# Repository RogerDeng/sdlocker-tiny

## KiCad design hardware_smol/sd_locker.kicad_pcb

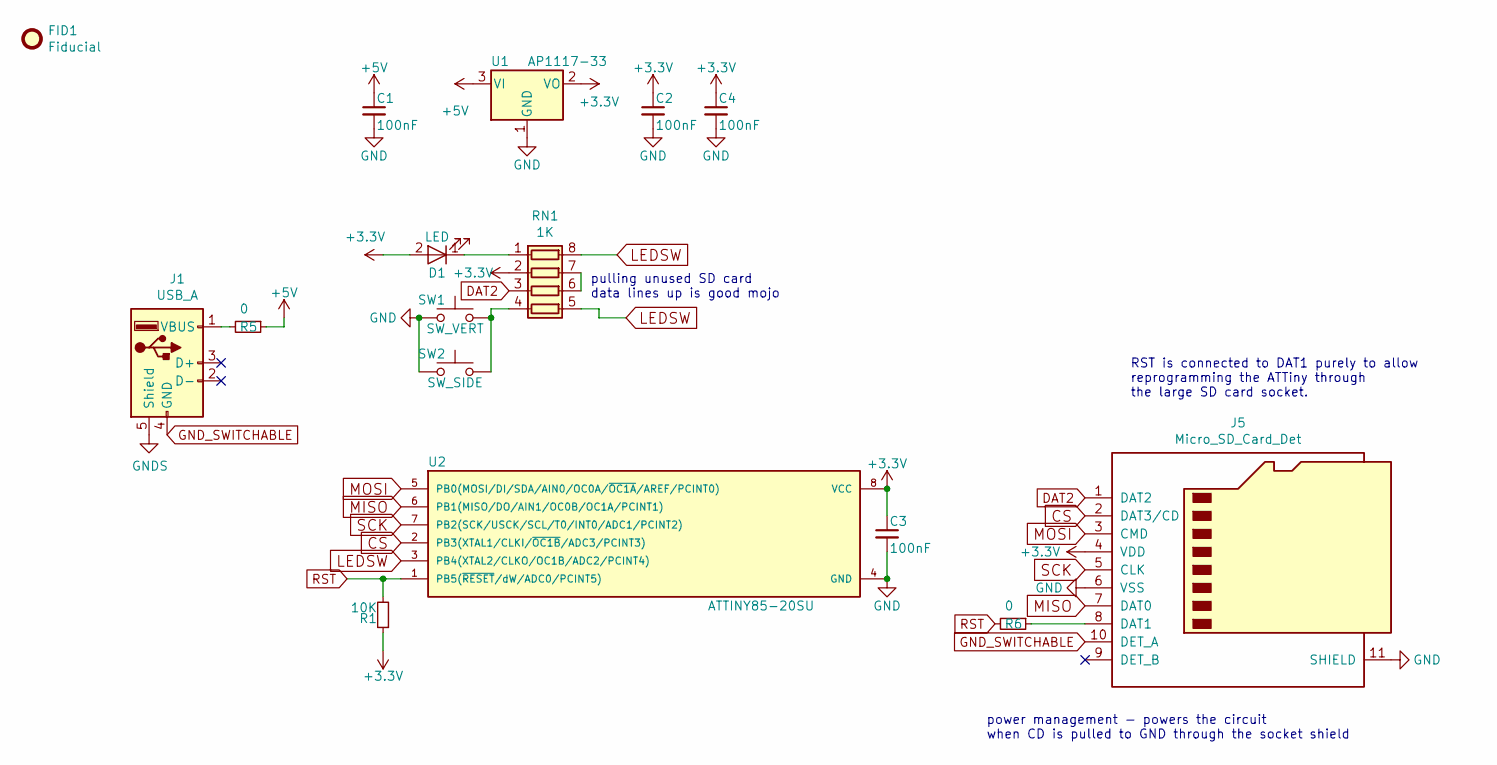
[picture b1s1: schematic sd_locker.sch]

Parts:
C1, C2, C3, C4: 100nF; C_0805_100nF_HandSoldering
D1: LED; LED_0805_HandSoldering
FID1: Fiducial; Fiducial_1.5mm_Mask3mm
J1: USB_A; USB_A_CNCTech_1001-011-01101_Horizontal
J5: Micro_SD_Card_Det; microSD-Receptacle-SelfEject
R1: 10K; R_0805_10K_HandSoldering
R5, R6: 0; R_0603_1608Metric_Pad1.05x0.95mm_HandSolder
RN1: 1K; R_Array_Concave_4x0402
SW1: SW_VERT; SW_SPST_EVQPE1
SW2: SW_SIDE; Panasonic_EVQPUL_EVQPUC
U1: AP1117-33; SOT-223-3_TabPin2
U2: ATTINY85-20SU; SOIJ-8_5.3x5.3mm_Pitch1.27mm

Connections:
+3V3: C2.1, C3.1, C4.1, D1.2 (A), J5.4 (VDD), R1.1, RN1.2 (R2.1), U1.2 (VO), U2.8 (VCC)
+5V: C1.1, R5.1, U1.3 (VI)
CS: J5.2 (DAT3/CD), U2.2 (PB3(XTAL1/CLKI/~OC1B~/ADC3/PCINT3))
DAT2: J5.1 (DAT2), RN1.3 (R3.1)
GND: C1.2, C2.2, C3.2, C4.2, J5.6 (VSS), J5.11 (SHIELD), SW1.2, SW2.2, U1.1 (GND), U2.4 (GND)
GNDS: J1.5 (Shield)
GND_SWITCHABLE: J1.4 (GND), J5.10 (DET_A)
LEDSW: RN1.5 (R4.2), RN1.8 (R1.2), U2.3 (PB4(XTAL2/CLKO/OC1B/ADC2/PCINT4))
MISO: J5.7 (DAT0), U2.6 (PB1(MISO/DO/AIN1/OC0B/OC1A/PCINT1))
MOSI: J5.3 (CMD), U2.5 (PB0(MOSI/DI/SDA/AIN0/OC0A/~OC1A~/AREF/P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)
unnamed: D1.1 (K), RN1.1 (R1.1)
unnamed: J1.1 (VBUS), R5.2
unnamed: J5.8 (DAT1), R6.1
unnamed: RN1.4 (R4.1), SW1.1, SW2.1
unnamed: RN1.6 (R3.2), RN1.7 (R2.2)
RST: R1.2, R6.2, U2.1 (PB5(~RESET~/dW/ADC0/PCINT5))
SCK: J5.5 (CLK), U2.7 (PB2(SCK/USCK/SCL/T0/INT0/ADC1/PCINT2))

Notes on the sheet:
RST is connected to DAT1 purely to allow reprogramming the ATTiny through the large SD card socket.
power management - powers the circuit when CD is pulled to GND through the socket shield
pulling unused SD card data lines up is good mojo

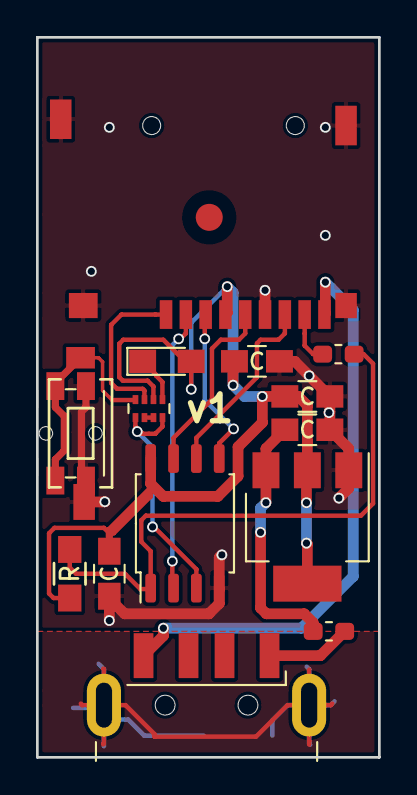
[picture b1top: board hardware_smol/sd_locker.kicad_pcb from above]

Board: 2 copper layers, 19.0 x 40.0 mm, 16 parts (0 on the bottom side), 16 nets.

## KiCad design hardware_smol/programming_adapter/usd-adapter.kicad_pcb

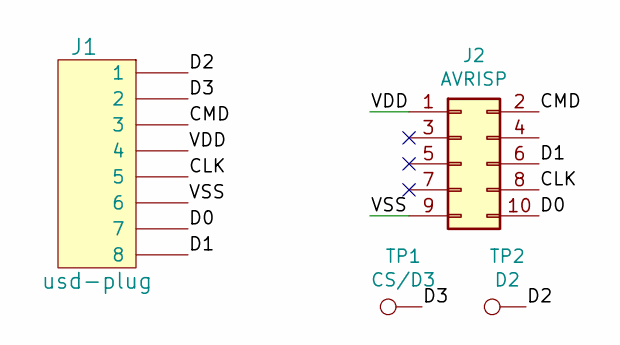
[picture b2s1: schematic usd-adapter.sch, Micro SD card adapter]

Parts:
J1: usd-plug; usd
J2: AVRISP; Side_2x5_Connector_SMD
TP1: CS/D3; TestPoint_Pad_1.0x1.0mm
TP2: D2; TestPoint_Pad_1.0x1.0mm

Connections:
/CLK: J1.5, J2.8
/CMD: J1.3, J2.2
/D0: J1.7, J2.10
/D1: J1.8, J2.6
/D2: J1.1, TP2.1
/D3: J1.2, TP1.1
/VDD: J1.4, J2.1
/VSS: J1.6, J2.9

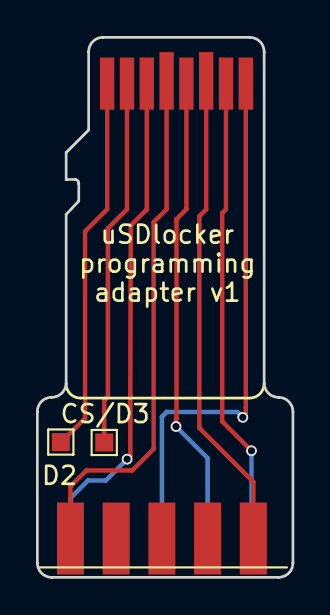
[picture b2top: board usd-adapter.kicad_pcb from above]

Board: 2 copper layers, 14.2 x 30.0 mm, 4 parts (0 on the bottom side), 8 nets.

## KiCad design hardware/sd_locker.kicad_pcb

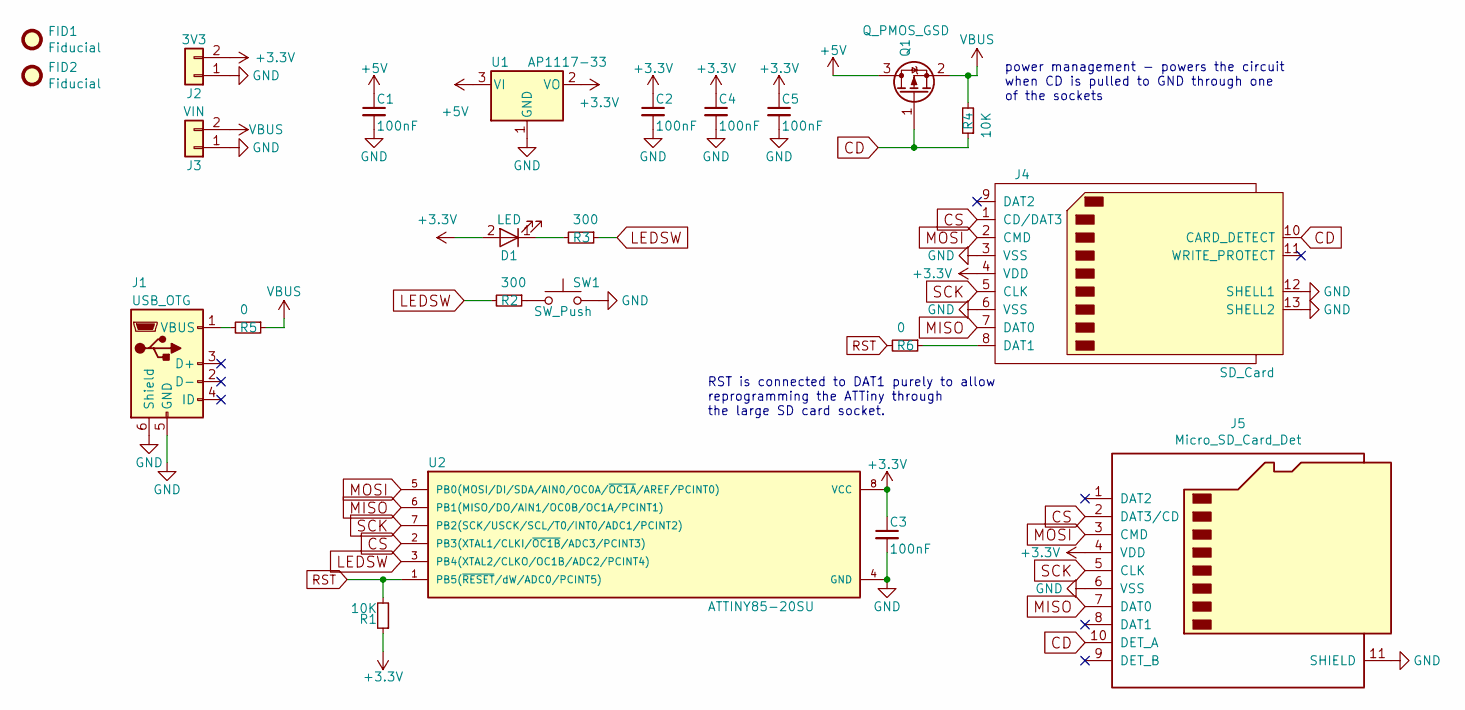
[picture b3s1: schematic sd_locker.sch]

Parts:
C1, C2, C3, C4, C5: 100nF; C_0805_100nF_HandSoldering
D1: LED; LED_0805_HandSoldering
FID1, FID2: Fiducial; Fiducial_1.5mm_Mask3mm
J1: USB_OTG; MICROUSB_SIMPLE
J2: 3V3; Pin_Header_Straight_1x02_Pitch2.54mm
J3: VIN; Pin_Header_Straight_1x02_Pitch2.54mm
J4: SD_Card; SD_Slot
J5: Micro_SD_Card_Det; microSD-Receptacle-SelfEject
Q1: Q_PMOS_GSD; IRLML6401-SOT-23_Handsoldering
R1, R4: 10K; R_0805_10K_HandSoldering
R2, R3: 300; R_0603_HandSoldering
R5, R6: 0; R_0603_1608Metric_Pad1.05x0.95mm_HandSolder
SW1: SW_Push; SW_SPST_EVQPE1
U1: AP1117-33; SOT-223-3_TabPin2
U2: ATTINY85-20SU; SOIJ-8_5.3x5.3mm_Pitch1.27mm

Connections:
+3V3: C2.1, C3.1, C4.1, C5.1, D1.2 (A), J2.2, J4.4 (VDD), J5.4 (VDD), R1.1, U1.2 (VO), U2.8 (VCC)
+5V: C1.1, Q1.3 (D), U1.3 (VI)
CD: J4.10 (CARD_DETECT), J5.10 (DET_A), Q1.1 (G), R4.1
CS: J4.1 (CD/DAT3), J5.2 (DAT3/CD), U2.2 (PB3(XTAL1/CLKI/~OC1B~/ADC3/PCINT3))
GND: C1.2, C2.2, C3.2, C4.2, C5.2, J1.5 (GND), J1.6 (Shield), J2.1, J3.1, J4.3 (VSS), J4.6 (VSS), J4.12 (SHELL1), J4.13 (SHELL2), J5.6 (VSS), J5.11 (SHIELD), SW1.2, U1.1 (GND), U2.4 (GND)
LEDSW: R2.2, R3.1, U2.3 (PB4(XTAL2/CLKO/OC1B/ADC2/PCINT4))
MISO: J4.7 (DAT0), J5.7 (DAT0), U2.6 (PB1(MISO/DO/AIN1/OC0B/OC1A/PCINT1))
MOSI: J4.2 (CMD), J5.3 (CMD), U2.5 (PB0(MOSI/DI/SDA/AIN0/OC0A/~OC1A~/AREF/P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)
unnamed: D1.1 (K), R3.2
unnamed: J1.1 (VBUS), R5.2
unnamed: J4.8 (DAT1), R6.1
unnamed: R2.1, SW1.1
RST: R1.2, R6.2, U2.1 (PB5(~RESET~/dW/ADC0/PCINT5))
SCK: J4.5 (CLK), J5.5 (CLK), U2.7 (PB2(SCK/USCK/SCL/T0/INT0/ADC1/PCINT2))
VBUS: J3.2, Q1.2 (S), R4.2, R5.1

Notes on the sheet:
RST is connected to DAT1 purely to allow reprogramming the ATTiny through the large SD card socket.
power management - powers the circuit when CD is pulled to GND through one of the sockets

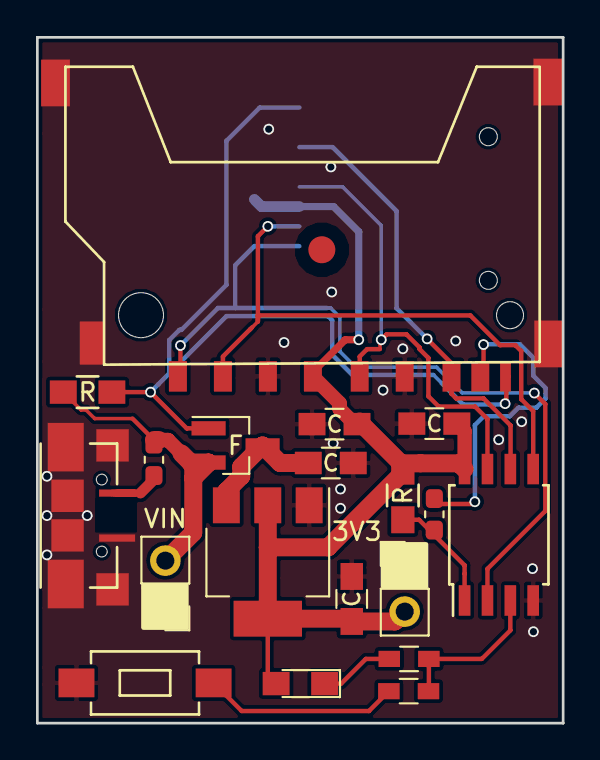
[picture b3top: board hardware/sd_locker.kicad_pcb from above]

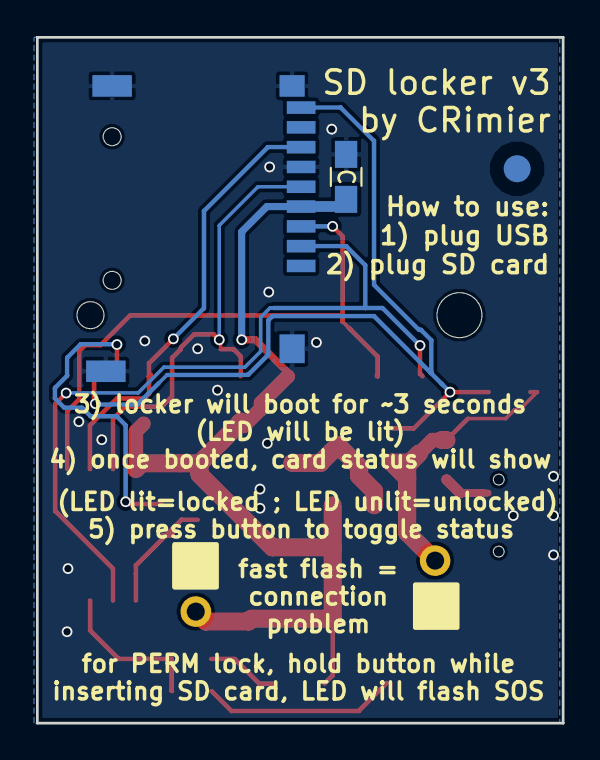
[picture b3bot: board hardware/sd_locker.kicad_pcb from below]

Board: 2 copper layers, 29.2 x 38.1 mm, 23 parts (3 on the bottom side), 15 nets.

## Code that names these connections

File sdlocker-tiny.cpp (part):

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 *
 *              ATMEL ATTINY85
 *                   +-v-+
 *      nc     PB5  1|   |8  Vcc --- +3.3V
 *      CS <-- PB3  2|   |7  PB2 --> SCK
 *   LEDSW <-> PB4  3|   |6  PB1 <-- MISO
 *     GND --- GND  4|   |5  PB0 --> MOSI
 *                   +---+
 *
 *
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 * The ATTINY85 doesn't have enough I/O pins so we need to share one.
 * Note the LED output is active low.
 */
#define LEDSW_PORT      PORTB
#define LEDSW_DDR       DDRB
#define LEDSW_PIN       PINB
#define LEDSW_BIT       4
#define LEDSW_MASK      (1<<LEDSW_BIT)

#define LEDSW_AS_LED    (LEDSW_DDR|=LEDSW_MASK)     // make the line an output
#define LEDSW_AS_SW     (LEDSW_DDR&=~LEDSW_MASK)    // make the line an input

#define TURN_LED_ON     (LEDSW_PORT&=~LEDSW_MASK)   // set line low, led on
#define TURN_LED_OFF    (LEDSW_PORT|=LEDSW_MASK)    // set line high, led off
#define SW_PULLUP       TURN_LED_OFF                // set line high, enable pullup
#define SW_GET_STATE    !(LEDSW_PIN & LEDSW_MASK)   // get switch state (1 = pressed)


/*
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/*
 * ReadSwitchOnce()
 * Checks if the switch is closed. NO debouncing.
 * Also handles I/O switching for the shared LEDSW pin, so that line
 * is always set as an output (LED) outside of this function.
 */
static uint8_t ReadSwitchOnce(void)
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
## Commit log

2018-12-15 gitignore-ing useless autogenerated files (except .hex)
2018-12-15 I have broken pinout on rev1 of my PCBs, working around some of it in software
2018-12-15 Added PERM bit support and dynamic TMP-to-PERM switching when the button is pressed on boot
2018-12-15 Small formatting changes
2018-12-15 Latest .hex (normal pinout)
2018-12-16 Adding hardware - v1, broken
2019-11-03 Fixing the SD slot footprint to match the pinout of the KiCad SD card holder symbol, adding the card detect pin
2019-11-03 Adding the 3D model for the SD slot
2019-11-03 Unverified - fixing the SD locker PCB layout so that airwires are not needed for SD slot connection, adding proper CD wire, adding 0R resistor for easier "battery-powered SD locker" modding
2019-11-19 Latest hardware version (v2) added
2019-11-19 Adding a fiducial on the bottom layer
2021-09-25 Latest hardware revision, v3, wasn't uplaoded for a long time - fixed
2021-09-25 removing the BROKEN_PINOUT code since it was 1) glitchy 2) unnecessary
2021-09-25 Adding a statically-generated CRC table which allows this code to work on a Tiny45, with RAM to spare. Commenting out runtime CRC table generation code, just in case - that's how git works, right?
2021-09-25 Switching default makefile to usbasp-clone since that's what people will most likely use with my hardware
2021-09-25 Adding fuse settings to the default makefile
2021-09-25 adding -O2 to make - uhh, just in case?
2021-09-25 Removing long-unused variable
2021-09-25 Adding latest .hex for ATTiny85
2022-03-17 Adding uSDlocker hardware files

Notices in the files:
hardware_smol/programming_adapter/usd-adapter.kicad_pcb:
Copyright (c) 2016 Samsung Electronics Co., Ltd All Rights Reserved
